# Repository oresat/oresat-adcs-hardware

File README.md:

# oresat-adcs-hardware

For more information on the OreSat project, please see <https://www.oresat.org/>!

## About this Repo

This repo contains the following projects:

* **The OreSat ADCS Card**
   * ADCS M0 microcontroller on its own OreSat Power Domain (OPD)
      * Power switch and LTC4300 that connects the M0 to:
         * BMI088 IMU (onboard the ADCS card)
         * LTC4305 2-Channel I2C Bus Multiplexer (one on each end cap via the backplane, end cards, and connectors to the end caps)
            * Two MMC5883MA magnetometers (two on each end cap, multiplexed by the LTC4305s)
      * Three STSPIN250s for the X, Y, and Z magnetorquers
   * Q1 Reaction Wheel OPD which powers the Q1 RW board
   * Q2 Reaction Wheel OPD which powers the Q2 RW board
   * Q3 Reaction Wheel OPD which powers the Q3 RW board
   * Q4 Reaction Wheel OPD which powers the Q4 RW board
* **OreSat RW boards**
   * Boards that run one of the four reaction wheels that we have.
   * Note that the "flat" version of the boards are for development

## LICENSE

Copyright the Portland State Aerospace Society, 2022.

This source describes Open Hardware that is licensed under CERN-OHL-S v2, or any later version.

You may redistribute and modify this source and make products using it under the terms of the CERN-OHL-S v2 (https://ohwr.org/cern_ohl_s_v2.txt).

This source is distributed WITHOUT ANY EXPRESS OR IMPLIED WARRANTY, INCLUDING OF MERCHANTABILITY, SATISFACTORY QUALITY AND FITNESS FOR A PARTICULAR PURPOSE. Please see the CERN-OHL-S v2 for applicable conditions.

Source location: https://github.com/oresat/

As per CERN-OHL-S v2 section 4, should You produce hardware based on this source, You must where practicable maintain the Source Location visible on the external case of the Gizmo or other products you make using this source.

# DEPRECATED - PLEASE EVENTUALLY REWRITE :)

## The OreSat Project
OreSat is an inter university collaboration to design an orbital vehicle. Once in orbit, the nanosatellite will engage in three missions. One of the missions is space testing a relatively new photovoltaic panel. The other missions require the ability to point at and maintain visual contact with a specified location. 
## Background Motivation   
In order to successfully complete these missions, OreSat will need to be able to articulate its orientation as well as its passive “drifting” spin (we’ll discuss what “passive spin” means a little later). 
Quick and reliable orientation adjustment and control will serve several purposes. It will allow the vehicle to direct its main camera, as well as giving it the ability to execute maneuvers that allow it to maintain visual and radio contact with a specific location. This makes taking photos and videos much easier, but it also allows us to have a segment of time to do large bandwidth data dumps to ground stations. This gives it the potential to do live video streaming. 
### Active Pointing
The method that was selected for active orientation on OreSat employs the use of internal spinning masses called reaction wheels. The basic principle is simple. If there is a free floating object and a section of it starts to spin, the rest of the body will react by spinning in the opposite direction. The spin rates are related, but not necessarily the same. If you’d like to look more into this, the concept is conservation of angular momentum. 
So the idea is that we have a pointing vector for Oresat (not poynting, that comes later), and an idea of the pointing vector to the location we would like to image. We simply take the difference, and then rotate the collective mass of all of the reaction wheels in the opposite direction until the satellite camera sees what we want it too.  
### Passive Spin Control
The term “passive spin” will be used to refer the net angular momentum of the nanosatellite. While the reaction wheels are active, they are able to control the direction and spin of the frame of the satellite, but only by effectively redistributing the momentum from the frame into the reaction wheel masses. The reaction wheels are incapable of altering the net angular momentum. The need for being able to modify the net momentum vector of the satellite helps alleviate the burden of two issues. The issues are thermal regulation and power generation. OreSat only has photovoltaic panels of its elongated faces. To maximize the amount of power, the desired passive spin of the satellite would put the long axis perpendicular to the sun. This maximizes the surface of exposure. There is another part to the total momentum though, and that is its magnitude. The rate of spin effects several things, but most notably it affects the temperature gradient experience by OreSat. If the satellite has no spin, then the side that the sun is hitting will heat continuously until OreSat passes behind the earth. This can cause several issues, most simply that having a hot spot would increase the likelihood of an electrical system to failing. Another issue is that the hot spot will cause different amounts of expansion in different areas of the frame, increasing the likelihood of failure. Another issue that hot spots cause is a drop in efficiency of the solar panels, making rotation partially an energy problem as well. 
Adding an intentional spin to OreSat will even out the thermal load applied to 

The attitude control system (ACS) inside oresat needs to orientate the position of the cubesat in space. This will be acheived in two ways; With brushless DC motors (BLDC) and with Magnetorquers. We are designing a PCB that controls both systems.

Find the project design contraints at,
[Project Design Constraints](https://github.com/oresat/oresat-acs-board/blob/master/Project%20Design%20Constraints.md)

ACS Level 2 Block Diagram Version 3.2

### System Hardware Overview
[Deatailed Hardware Reference Guide](https://github.com/oresat/oresat-acs-board/tree/master/Component%20File)

### EagleCAD Files:
[Link to the EagleCAD schematics and board layouts](https://github.com/oresat/oresat-acs-board/tree/master/eaglecad)

### Manufacturing Photos:
[Manufacturing photos of board layouts and CAD model of mounting strategy](https://github.com/oresat/oresat-acs-board/tree/master/Manufacturing%20photos)

### Capstone Poster:
[Link to Capstone poster in Google Drive](https://docs.google.com/presentation/d/1KBfbX376Y7nvsIXe14JdyOgP9TMmgJlgeOiYP8BOekc/edit#slide=id.p1)

### System Firmware:
[Check here for the firmware information](https://github.com/oresat/oresat-firmware/wiki/ACS-Firmware)

### Research and Tutorials / Ramp Up Documents:
Brushless DC (BLDC) motor control is a challenging form of motor control. We found numerous helpful tutorials and references.
[Link to research references and bibliography, start here for a ramp up on ACS](https://github.com/oresat/oresat-acs-board/blob/master/Ramp%20Up.md)

## Final Product:

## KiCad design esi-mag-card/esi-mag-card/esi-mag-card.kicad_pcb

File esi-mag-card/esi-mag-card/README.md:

---
title: "**OreSat Mag Card**"
subtitle: |
  **Fabrication and Assembly Information**\
  For build TIME-STAMP
fontsize: 10pt
geometry:
  - margin=0.5in
toc: true
toc-depth: 2
colorlinks: true
urlcolor: blue
---

\newpage

# About this Board

## Board Description

The OreSat Mag Card handles three things for the open source [OreSat CubeSat system](https://www.oresat.org/):

- Reads the four magnetometers located on the end caps of the satellite and broadcasts the data on the CAN bus.
- Reads the 6 DOF inertial measurement unit (IMU) and broadcasts the data on the CAN bus (mostly just the gyroscopes).
- Runs the three magnetorquers based on commands from the C3 via the CAN bus.

## Documentation Links

- Mag card hardware Git repository: <https://github.com/oresat/oresat-adcs-hardware>
- **TODO:** Mag card Design Notes + Design Review Notes

## Documentation Files

| Filename                        | Notes                                    |
| ------------------------------- | ---------------------------------------- |
| README.pdf                      | This README file                         |
| PROJECT-NAME-outline.dxf        | Board outline (with holes) in DXF format |
| PROJECT-NAME-pcba.step          | 3D model of PCBA (with components)       |
| PROJECT-NAME-render-bot.jpg     | Render of the top of the 3D model        |
| PROJECT-NAME-render-bot.jpg     | Render of the bottom of the 3D model     |
| PROJECT-NAME-schematic.pdf      | PDF of board schematics                  |

## Contact Information

- Website: <https://www.oresat.org/>
- Email: <oresat@pdx.edu>
- Instagram: @pdxaerospace

## Board Renders

{width=50%}
{width=50%}

\newpage

# Printed Circuit Board (PCB) Fabrication Information

## Board Info

- 4 layer board
- Bounding box is 99.8 x 94.6 mm (3.93 x 3.72 in)
- Board thickness is 1.59 mm (0.063 inch)

## Board Requirements

- Design Rules
    - Minimum Trace / Space design rules
       - Outer layers: 0.127 mm (5.0 mil) / 0.127 mm (5.0 mil)
       - Inner layers: 0.127 mm (5.0 mil) / 0.127 mm (5.0 mil)
    - Outer dimension router tolerance: +/- 0.254 mm (10.0 mil)
    - Hole placement tolerance: +/- 0.075 mm (3.0 mil)
    - Inner tab routed slot tolerance: +/- 0.254 mm (10.0 mil)
- Drills
   - Drill Positional Tolerance: 0.051 mm (2.0 mil)
   - Drill Size tolerance: +/- 0.064 mm (2.5 mil)
- Plated/Un-plated holes
  - There are 8 un-plated (NPT) holes
  - There are 730 plated through (PTH) holes
  - PTH minimum diameter: 0.254 mm (10 mil)
  - PTH minimum annulus: 0.102 mm (4 mil) radius
- Outline/Routing
  - Requires a 1.0 mm or smaller diameter routing bit
- Slots/Cutouts
  - There is one cutout.
- There are 3 fiducials on the top layer.
- Panel tabs ("mouse bites")
   - Card edges must be smooth; no mouse bites or other intrusions into the card outline.
   - If external mouse bites are required, minimize and customer will remove by hand before assembly.
- If not otherwise specified, build to IPC 6012 Class 2 or better.

## Materials

- No controlled impedance.
- Outer layers must be 1 oz Copper, inner layers can be 0.5 or 1.0 oz Copper.
- Isola FR408HR or material recommended.
- Board Surface treatment should be ENIG, althogh immersion Silver is acceptable.
- White silkscreen on top and bottom surface
- Taiyo PSR-4000 or equivalent soldermask on top and bottom, no requirements for color.

## Suggested Stack Up

| Layer         | Thickness           | Notes                                        |
|---------------|---------------------|----------------------------------------------|
| Top Copper    | 0.043 mm /  1.7 mil |  Layer 1 foil, 1 oz Cu after plating         |
| prepreg       | 0.200 mm /  7.9 mil |  Prepreg - Isola FR408HR 2113                |
| Layer 2       | 0.018 mm /  0.7 mil |  Layer 2 foil, 0.5 oz Cu                     |
| Core          | 0.991 mm /   39 mil |  Core Isola FR408HR                          |
| Layer 3       | 0.018 mm /  0.7 mil |  Layer 3 foil, 0.5 oz Cu                     |
| prepreg       | 0.200 mm /  7.9 mil |  Prepreg - Isola FR408HR 2113                |
| Bottom Copper | 0.043 mm /  1.7 mil |  Layer 4 foil, 1 oz copper after plating     |
| **Total Stackup** | **1.588 mm / 62.5 mil** |                                      |

## Array / Panel Information

- Coordinate with Contract Manufacturer (CM) for optimal size of this panel.
- If no feedback from CM, then produce single boards (no panel).

## Fabrication Files

### IPC-2581 File

| Filename                 | Notes                                   |
| ------------------------ | --------------------------------------- |
| PROJECT-NAME-ipc2581.xml | IPC-2581 board information file         |

### Legacy PCB Files

| Filename                      | Notes                                         |
| ------------------------------| --------------------------------------------- |
| PROJECT-NAME-Edge_Cuts.gbr    | RS274X file for the dimension (outline) layer |
| PROJECT-NAME-F_Silkscreen.gbr | RS274X file for the top silkscreen            |
| PROJECT-NAME-F_Mask.gbr       | RS274X file for the top soldermask            |
| PROJECT-NAME-F_Cu.gbr         | RS274X file for the top copper layer          |
| PROJECT-NAME-In1_Cu.gbr       | RS274X file for the layer 2 copper            |
| PROJECT-NAME-In2_Cu.gbr       | RS274X file for the layer 3 copper            |
| PROJECT-NAME-B_Cu.gbr         | RS274X file for the bottom copper layer       |
| PROJECT-NAME-B_Mask.gbr       | RS274X file for the bottom soldermask         |
| PROJECT-NAME-B_Silkscreen.gbr | RS274X file for the bottom silkscreen         |
| PROJECT-NAME-NPTH.drl         | Excellon file for non-plated through holes    |
| PROJECT-NAME-PTH.drl          | Excellon file for plated through holes        | 

\newpage

# Printed Circuit Board Assembly (PCBA) Information

## Assembly Info

- This PCBA is surface mount (SMT) components with 4 through-hole (TH) components.
- Components are only on the top side of the board.

## Assembly Requirements

- Assemble to IPC Class 2 or better
- Bake components that are not moisture sealed to appropriate levels as required.
- Solder paste MUST be leaded.
- Aqueous flux and wash strongly preferred.
   - Clean to NASA Standard "Visibly Clean (VC)": No particles or residues are visible to the naked eye.
- No conformal coating.
- Ship in antistatic protective bag

## Component Specific Assembly Information

- No specific requirements.

## Assembly Files

### IPC-2581 File

| Filename                 | Notes                           |
| ------------------------ | ------------------------------- |
| PROJECT-NAME-ipc2581.xml | IPC-2581 board information file |

### Bill of Materials (BOM)

| Filename             | Description                            |
| -------------------- | -------------------------------------- |
| PROJECT-NAME-bom.csv | BOM in Comma Separated Variable format |

### Solder Paste Stencils

| Filename                 | Notes                                            |
| ------------------------ | ------------------------------------------------ |
| PROJECT-NAME-B_Paste.gbr | RS274X file for top/front solder paste stencil   |
| PROJECT-NAME-F_Paste.gbr | RS274X file for bottom/back solder paste stencil |

### Mounting/Placement Location

| Filename            | Description                                 |
| ------------------- | ------------------------------------------- |
| PROJECT-NAME-3u.pos | Pick and place locations for components     |

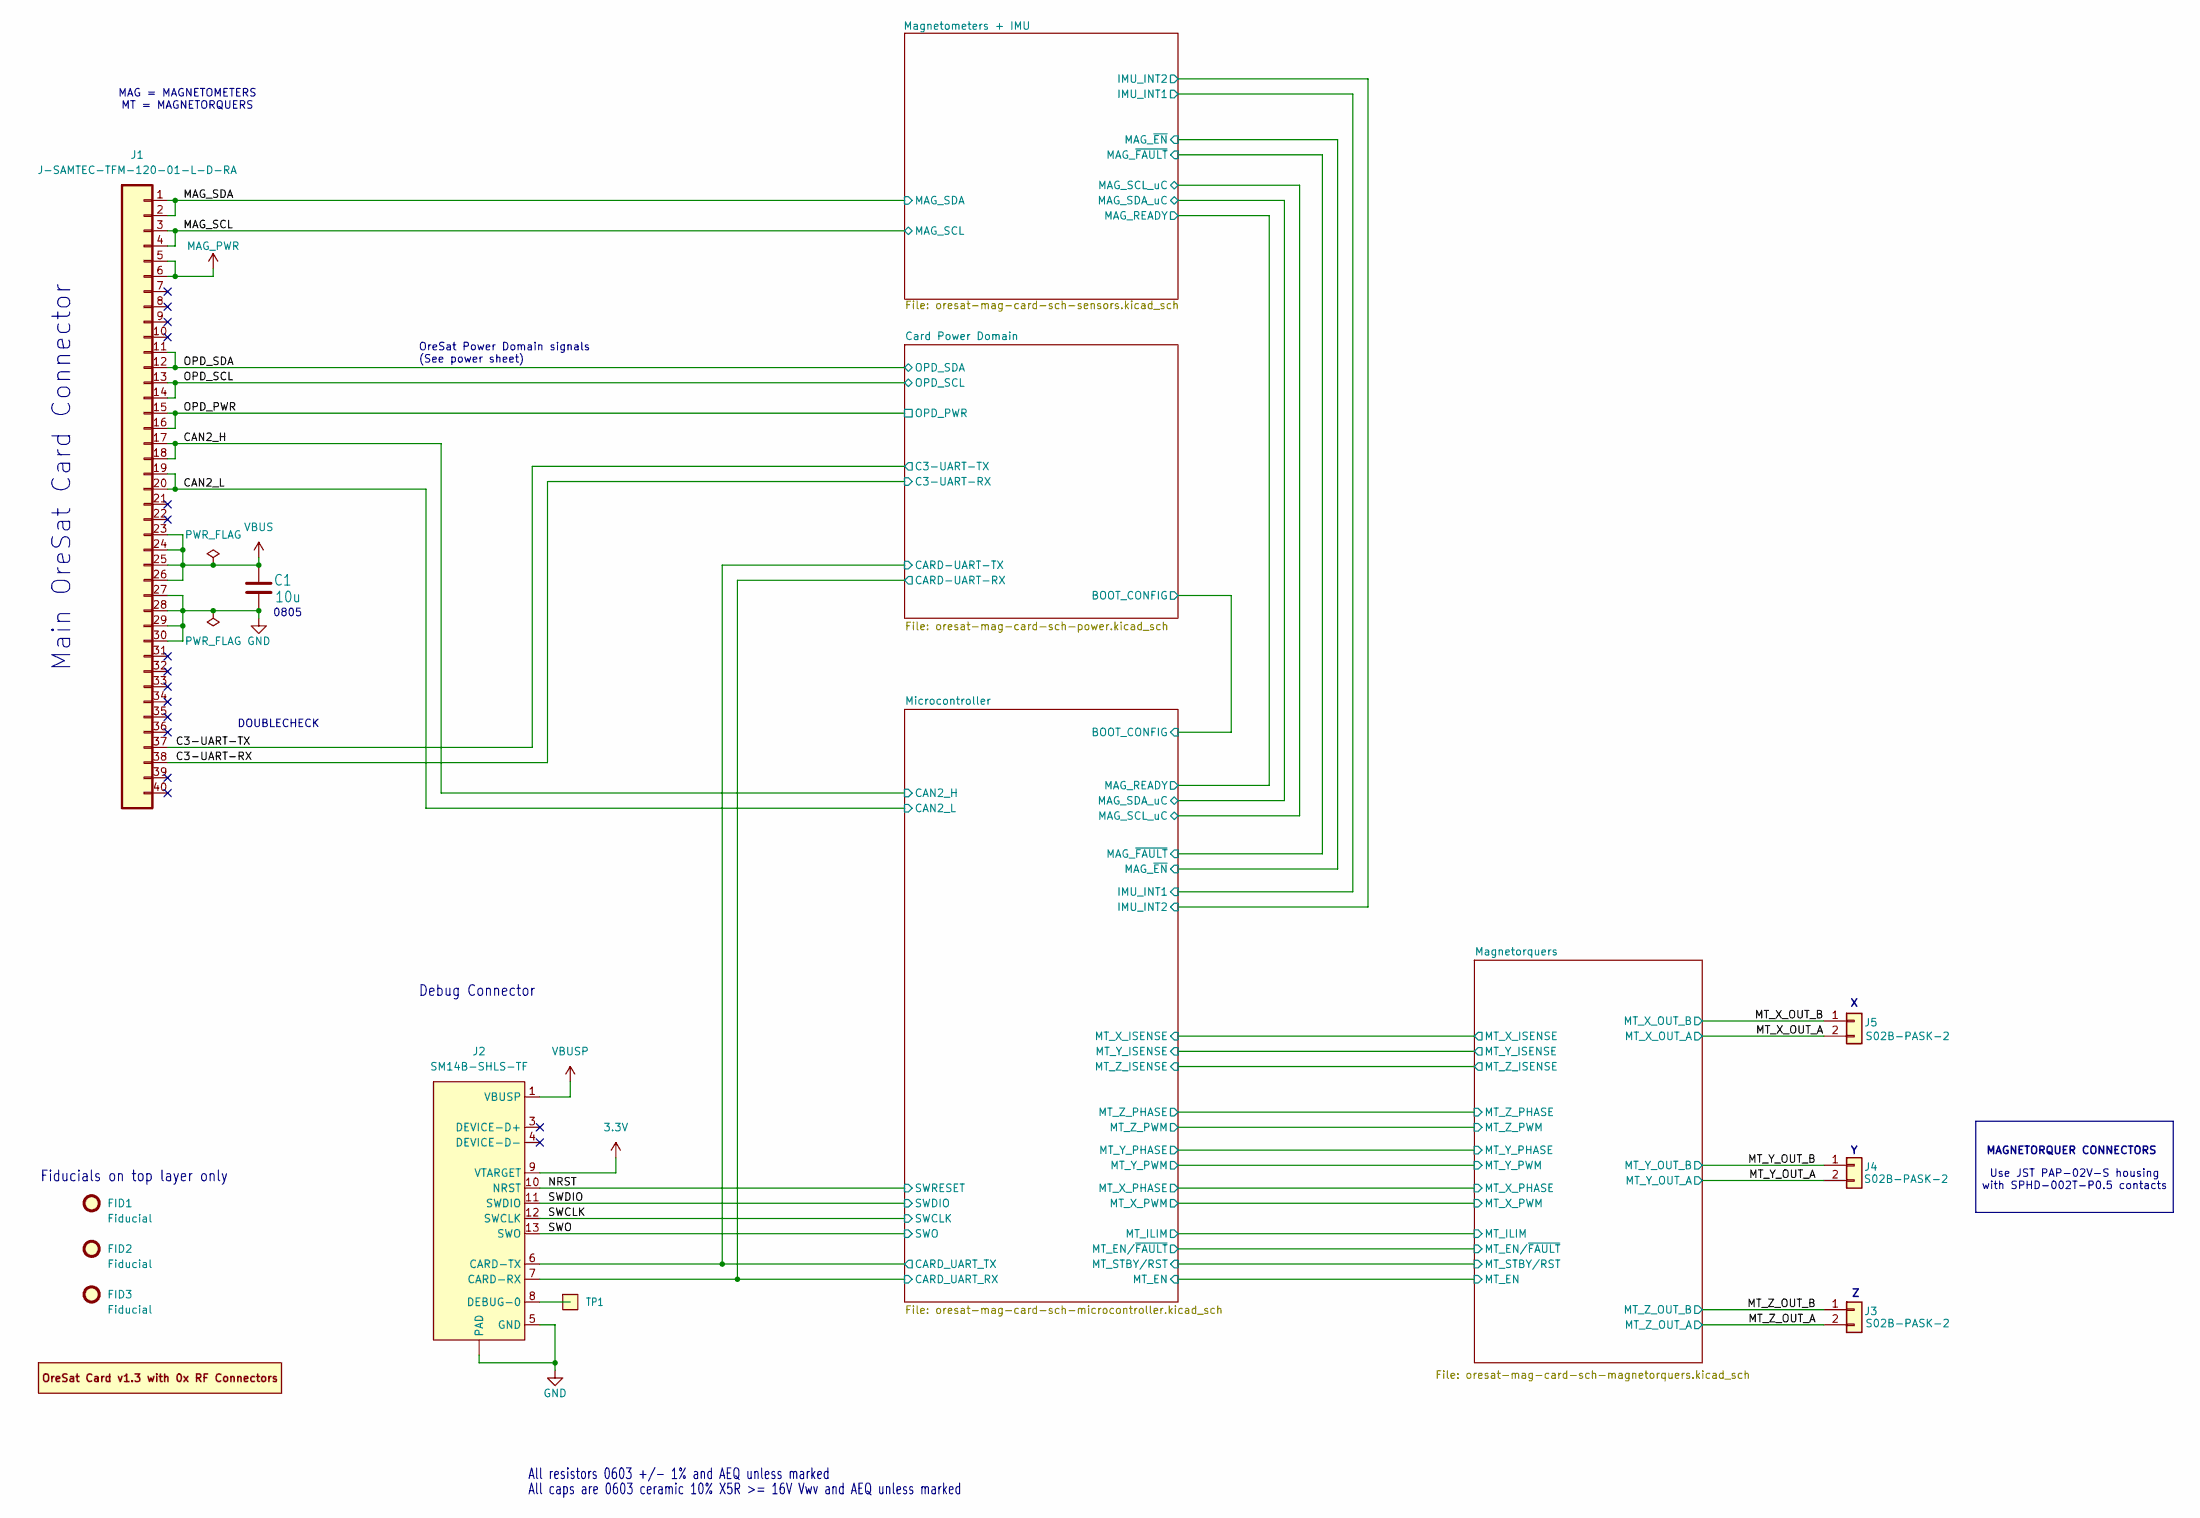
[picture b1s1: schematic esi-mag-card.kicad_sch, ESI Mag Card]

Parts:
C1: 10u; 0805-B-NOSILK; MPN GRT21BC71E106KE13K
FID1, FID2, FID3: Fiducial; Fiducial_1mm_Mask2mm
J1: J-SAMTEC-TFM-120-01-L-D-RA; J-SAMTEC-TFM-120-X1-XXX-D-RA; MPN TFM-120-01-L-D-RA
J2: SM14B-SHLS-TF; J-JST-SM14BSHLSTF; MPN SM14B-SHLS-TF
J3, J4, J5: S02B-PASK-2; JST-S02BPASK2LFSN; MPN S02B-PASK-2
PCB1: ORESAT-CARD-V1.3-GENERIC-0RF; ORESAT-CARD-V1.3-0RF; MPN N/A
TP1: Test-Point; TestPoint-0.75mm-th

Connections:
3.3V: J2.9 (VTARGET); also elsewhere on the board
/C3-UART-RX: J1.38; also elsewhere on the board
/C3-UART-TX: J1.37; also elsewhere on the board
/CAN2_H: J1.17, J1.18; also elsewhere on the board
/CAN2_L: J1.19, J1.20; also elsewhere on the board
/Card Power Domain/CARD-UART-RX: J2.7 (CARD-RX); also elsewhere on the board
/Card Power Domain/CARD-UART-TX: J2.6 (CARD-TX); also elsewhere on the board
/MAG_SCL: J1.3, J1.4; also elsewhere on the board
/MAG_SDA: J1.1, J1.2; also elsewhere on the board
/MT_X_OUT_A: J5.2; also elsewhere on the board
/MT_X_OUT_B: J5.1; also elsewhere on the board
/MT_Y_OUT_A: J4.2; also elsewhere on the board
/MT_Y_OUT_B: J4.1; also elsewhere on the board
/MT_Z_OUT_A: J3.2; also elsewhere on the board
/MT_Z_OUT_B: J3.1; also elsewhere on the board
/NRST: J2.10 (NRST); also elsewhere on the board
/OPD_PWR: J1.15, J1.16; also elsewhere on the board
/OPD_SCL: J1.13, J1.14; also elsewhere on the board
/OPD_SDA: J1.11, J1.12; also elsewhere on the board
/SWCLK: J2.12 (SWCLK); also elsewhere on the board
/SWDIO: J2.11 (SWDIO); also elsewhere on the board
/SWO: J2.13 (SWO); also elsewhere on the board
GND: C1.2, J1.27, J1.28, J1.29, J1.30, J2.5 (GND), J2.14 (GND), J2.15 (PAD), J2.16 (PAD); also elsewhere on the board
MAG_PWR: J1.5, J1.6; also elsewhere on the board
unnamed: J2.8 (DEBUG-0), TP1.1 (1_1)
VBUS: C1.1, J1.23, J1.24, J1.25, J1.26; also elsewhere on the board
VBUSP: J2.1 (VBUSP), J2.2 (VBUSP); also elsewhere on the board

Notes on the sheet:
All caps are 0603 ceramic 10% X5R >= 16V Vwv and AEQ unless marked
Main OreSat Card Connector
MAG = MAGNETOMETERS MT = MAGNETORQUERS
Use JST PAP-02V-S housing with SPHD-002T-P0.5 contacts
MAGNETORQUER CONNECTORS
DOUBLECHECK
Debug Connector
Fiducials on top layer only
0805
OreSat Power Domain signals (See power sheet)
All resistors 0603 +/- 1% and AEQ unless marked

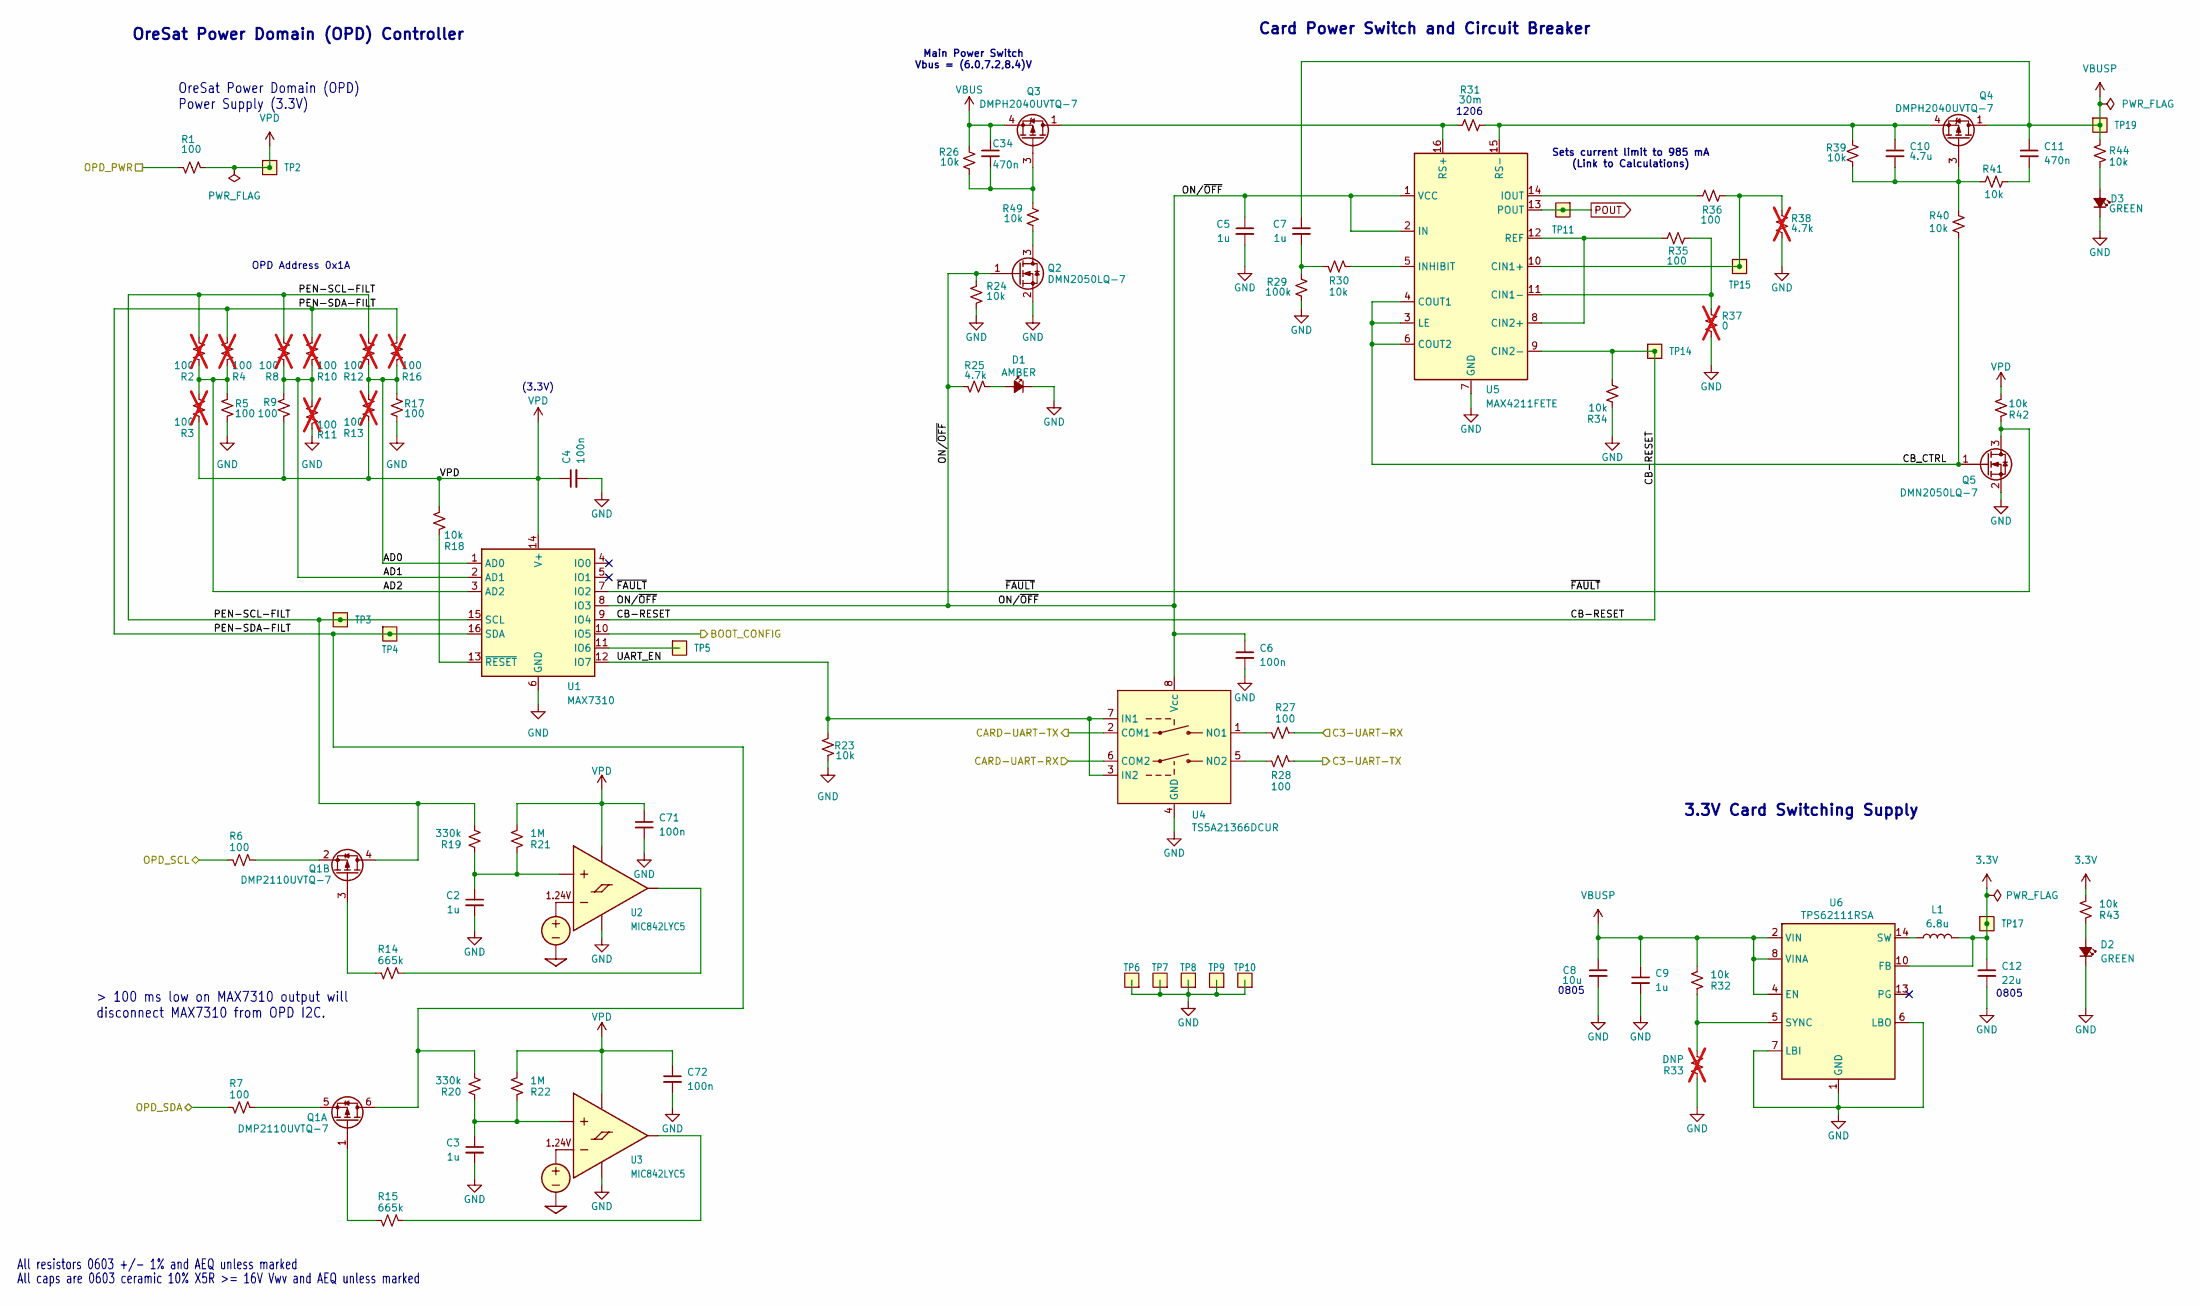
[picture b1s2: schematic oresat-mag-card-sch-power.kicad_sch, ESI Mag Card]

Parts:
C2, C3, C5, C7, C9: 1u; 0603-C-NOSILK; MPN GRT188R71E105KE13D
C4, C6, C71, C72: 100n; 0603-C-NOSILK; MPN C0603C104K5RACAUTO
C8: 10u; 0805-B-NOSILK; MPN GRT21BC71E106KE13K
C10: 4.7u; 0603-C-NOSILK; MPN GRT188C71C475KE13D
C11, C34: 470n; 0603-C-NOSILK; MPN C0603C474K3RACAUTO
C12: 22u; 0805-B-NOSILK; MPN GRT21BC81C226ME13L
D1: AMBER; LED_0603_1608Metric; MPN 150060AS75000
D2, D3: GREEN; LED_0603_1608Metric; MPN 150060GS75000
L1: 6.8u; L_ECS-MPI4040; MPN ECS-MPI4040R4-6R8-R
Q1: DMP2110UVTQ-7; SOT-23-6; MPN DMP2110UVTQ-7
Q2, Q5: DMN2050LQ-7; SOT-23; MPN DMN2050LQ-7
Q3, Q4: DMPH2040UVTQ-7; TSOT-23-6; MPN DMPH2040UVTQ-7
R1, R5, R6, R7, R9, R17, R27, R28, R35, R36: 100; 0603-C-NOSILK; MPN RMCF0603FT100R
R2, R3, R4, R8, R10, R11, R12, R13, R16: 100; 0603-C-NOSILK; MPN RMCF0603FT100R; not fitted
R14, R15: 665k; 0603-C-NOSILK; MPN RMCF0603FT665K
R18, R23, R24, R26, R30, R32, R34, R39, R40, R41, R42, R43, R44, R49: 10k; 0603-C-NOSILK; MPN RMCF0603FT10K0
R19, R20: 330k; 0603-C-NOSILK; MPN RMCF0603FT330K
R21, R22: 1M; 0603-C-NOSILK; MPN RMCF0603FT1M00
R25: 4.7k; 0603-C-NOSILK; MPN RMCF0603FT4K70
R29: 100k; 0603-C-NOSILK; MPN RMCF0603FT100K
R31: 30m; 1206-C; MPN CSR1206FK30L0
R33: DNP; 0603-C-NOSILK; not fitted
R37: 0; 0603-C-NOSILK; MPN RMCF0603ZT0R00; not fitted
R38: 4.7k; 0603-C-NOSILK; MPN RMCF0603FT4K70; not fitted
TP2, TP3, TP4, TP5, TP6, TP7, TP8, TP9, TP10, TP11, TP14, TP15, TP17, TP19: Test-Point; TestPoint-0.75mm-th
U1: MAX7310; QFN-16-1EP_4x4mm_P0.65mm_EP2.1x2.1mm; MPN MAX7310ATE+
U2, U3: MIC842LYC5; SOT-353_SC-70-5; MPN MIC842LYC5-TR
U4: TS5A21366DCUR; VSSOP-8_2.3x2mm_P0.5mm; MPN TS5A21366DCUR
U5: MAX4211FETE; QFN-16-1EP_4x4mm_P0.65mm_EP2.1x2.1mm; MPN MAX4211FETE
U6: TPS62111RSA; Texas_RSA_VQFN-16-1EP_4x4mm_P0.65mm_EP2.7x2.7mm; MPN TPS62111RSA

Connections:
3.3V: C12.1, L1.2, R43.2, TP17.1 (1_1), U6.10 (FB); also elsewhere on the board
/C3-UART-RX: R27.1; also elsewhere on the board
/C3-UART-TX: R28.1; also elsewhere on the board
/Card Power Domain/AD0: R12.1, R13.2, R16.1, R17.2, U1.1 (AD0)
/Card Power Domain/AD1: R8.1, R9.2, R10.1, R11.2, U1.2 (AD1)
/Card Power Domain/AD2: R2.1, R3.2, R4.1, R5.2, U1.3 (AD2)
/Card Power Domain/BOOT_CONFIG: U1.10 (IO5); also elsewhere on the board
/Card Power Domain/CARD-UART-RX: U4.6 (COM2); also elsewhere on the board
/Card Power Domain/CARD-UART-TX: U4.2 (COM1); also elsewhere on the board
/Card Power Domain/CB-RESET: R34.2, TP14.1 (1_1), U1.9 (IO4), U5.9 (CIN2-)
/Card Power Domain/CB_CTRL: Q5.1 (G), R40.1, U5.3 (LE), U5.4 (COUT1), U5.6 (COUT2)
/Card Power Domain/ON/~OFF: C5.1, C6.1, Q2.1 (G), R24.1, R25.2, U1.8 (IO3), U4.8 (Vcc), U5.1 (VCC), U5.2 (IN)
/Card Power Domain/PEN-SCL-FILT: Q1.4 (D), R2.2, R8.2, R12.2, R19.2, TP3.1 (1_1), U1.15 (SCL)
/Card Power Domain/PEN-SDA-FILT: Q1.6 (D), R4.2, R10.2, R16.2, R20.2, TP4.1 (1_1), U1.16 (SDA)
/Card Power Domain/UART_EN: R23.2, U1.12 (IO7), U4.3 (IN2), U4.7 (IN1)
/Card Power Domain/~FAULT: Q5.3 (D), R42.1, U1.7 (IO2)
/OPD_PWR: R1.2; also elsewhere on the board
/OPD_SCL: R6.2; also elsewhere on the board
/OPD_SDA: R7.2; also elsewhere on the board
GND: C2.2, C3.2, C4.2, C5.2, C6.2, C8.2, C9.2, C12.2, C71.2, C72.2, D1.1 (K), D2.1 (K), D3.1 (K), Q2.2 (S), Q5.2 (S), R5.1, R11.1, R17.1, R23.1, R24.2, R29.2, R33.1, R34.1, R37.2, R38.2, TP6.1 (1_1), TP7.1 (1_1), TP8.1 (1_1), TP9.1 (1_1), TP10.1 (1_1), U1.6 (GND), U1.17 (GND), U2.2 (GND), U3.2 (GND), U4.4 (GND), U5.7 (GND), U5.17 (GND), U6.1 (GND), U6.6 (LBO), U6.7 (LBI), U6.9 (GND), U6.11 (GND), U6.12 (GND), U6.16 (GND), U6.17 (GND); also elsewhere on the board
unnamed: C7.2, R29.1, R30.2
unnamed: C11.2, R41.1
unnamed: D1.2 (A), R25.1
unnamed: D2.2 (A), R43.1
unnamed: D3.2 (A), R44.1
unnamed: L1.1, U6.14 (SW), U6.15 (SW)
unnamed: Q1.1 (G), R15.2
unnamed: Q1.5 (S), R7.1
unnamed: Q1.3 (G), R14.2
unnamed: Q1.2 (S), R6.1
unnamed: Q2.3 (D), R49.2
unnamed: C34.2, Q3.3 (G), R26.2, R49.1
unnamed: C10.2, Q4.3 (G), R39.1, R40.2, R41.2
unnamed: C10.1, Q4.4 (S), R31.2, R39.2, U5.15 (RS-)
unnamed: TP5.1 (1_1), U1.11 (IO6)
unnamed: R18.1, U1.13 (~RESET)
unnamed: C2.1, R19.1, R21.1, U2.1 (INP)
unnamed: R14.1, U2.4 (OUT)
unnamed: C3.1, R20.1, R22.1, U3.1 (INP)
unnamed: R15.1, U3.4 (OUT)
unnamed: R27.2, U4.1 (NO1)
unnamed: R28.2, U4.5 (NO2)
unnamed: R36.1, R38.1, TP15.1 (1_1), U5.10 (CIN1+)
unnamed: R35.1, R37.1, U5.11 (CIN1-)
unnamed: R35.2, U5.8 (CIN2+), U5.12 (REF)
unnamed: R30.1, U5.5 (INHIBIT)
unnamed: R36.2, U5.14 (IOUT)
unnamed: Q3.1 (D), Q3.2 (D), Q3.5 (D), Q3.6 (D), R31.1, U5.16 (RS+)
unnamed: R32.1, R33.2, U6.5 (SYNC)
POUT: TP11.1 (1_1), U5.13 (POUT)
VBUS: C34.1, Q3.4 (S), R26.1; also elsewhere on the board
VBUSP: C7.1, C8.1, C9.1, C11.1, Q4.1 (D), Q4.2 (D), Q4.5 (D), Q4.6 (D), R32.2, R44.2, TP19.1 (1_1), U6.2 (VIN), U6.3 (VIN), U6.4 (EN), U6.8 (VINA); also elsewhere on the board
VPD: C4.1, C71.1, C72.1, R1.1, R3.1, R9.1, R13.1, R18.2, R21.2, R22.2, R42.2, TP2.1 (1_1), U1.14 (V+), U2.5 (VDD), U3.5 (VDD)

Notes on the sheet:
Sets current limit to 985 mA (Link to Calculations)
OPD Address 0x1A
3.3V Card Switching Supply
OreSat Power Domain (OPD) Power Supply (3.3V)
> 100 ms low on MAX7310 output will disconnect MAX7310 from OPD I2C.
Card Power Switch and Circuit Breaker
1206
(3.3V)
All resistors 0603 +/- 1% and AEQ unless marked
All caps are 0603 ceramic 10% X5R >= 16V Vwv and AEQ unless marked
OreSat Power Domain (OPD) Controller
0805
Main Power Switch Vbus = (6.0,7.2,8.4)V

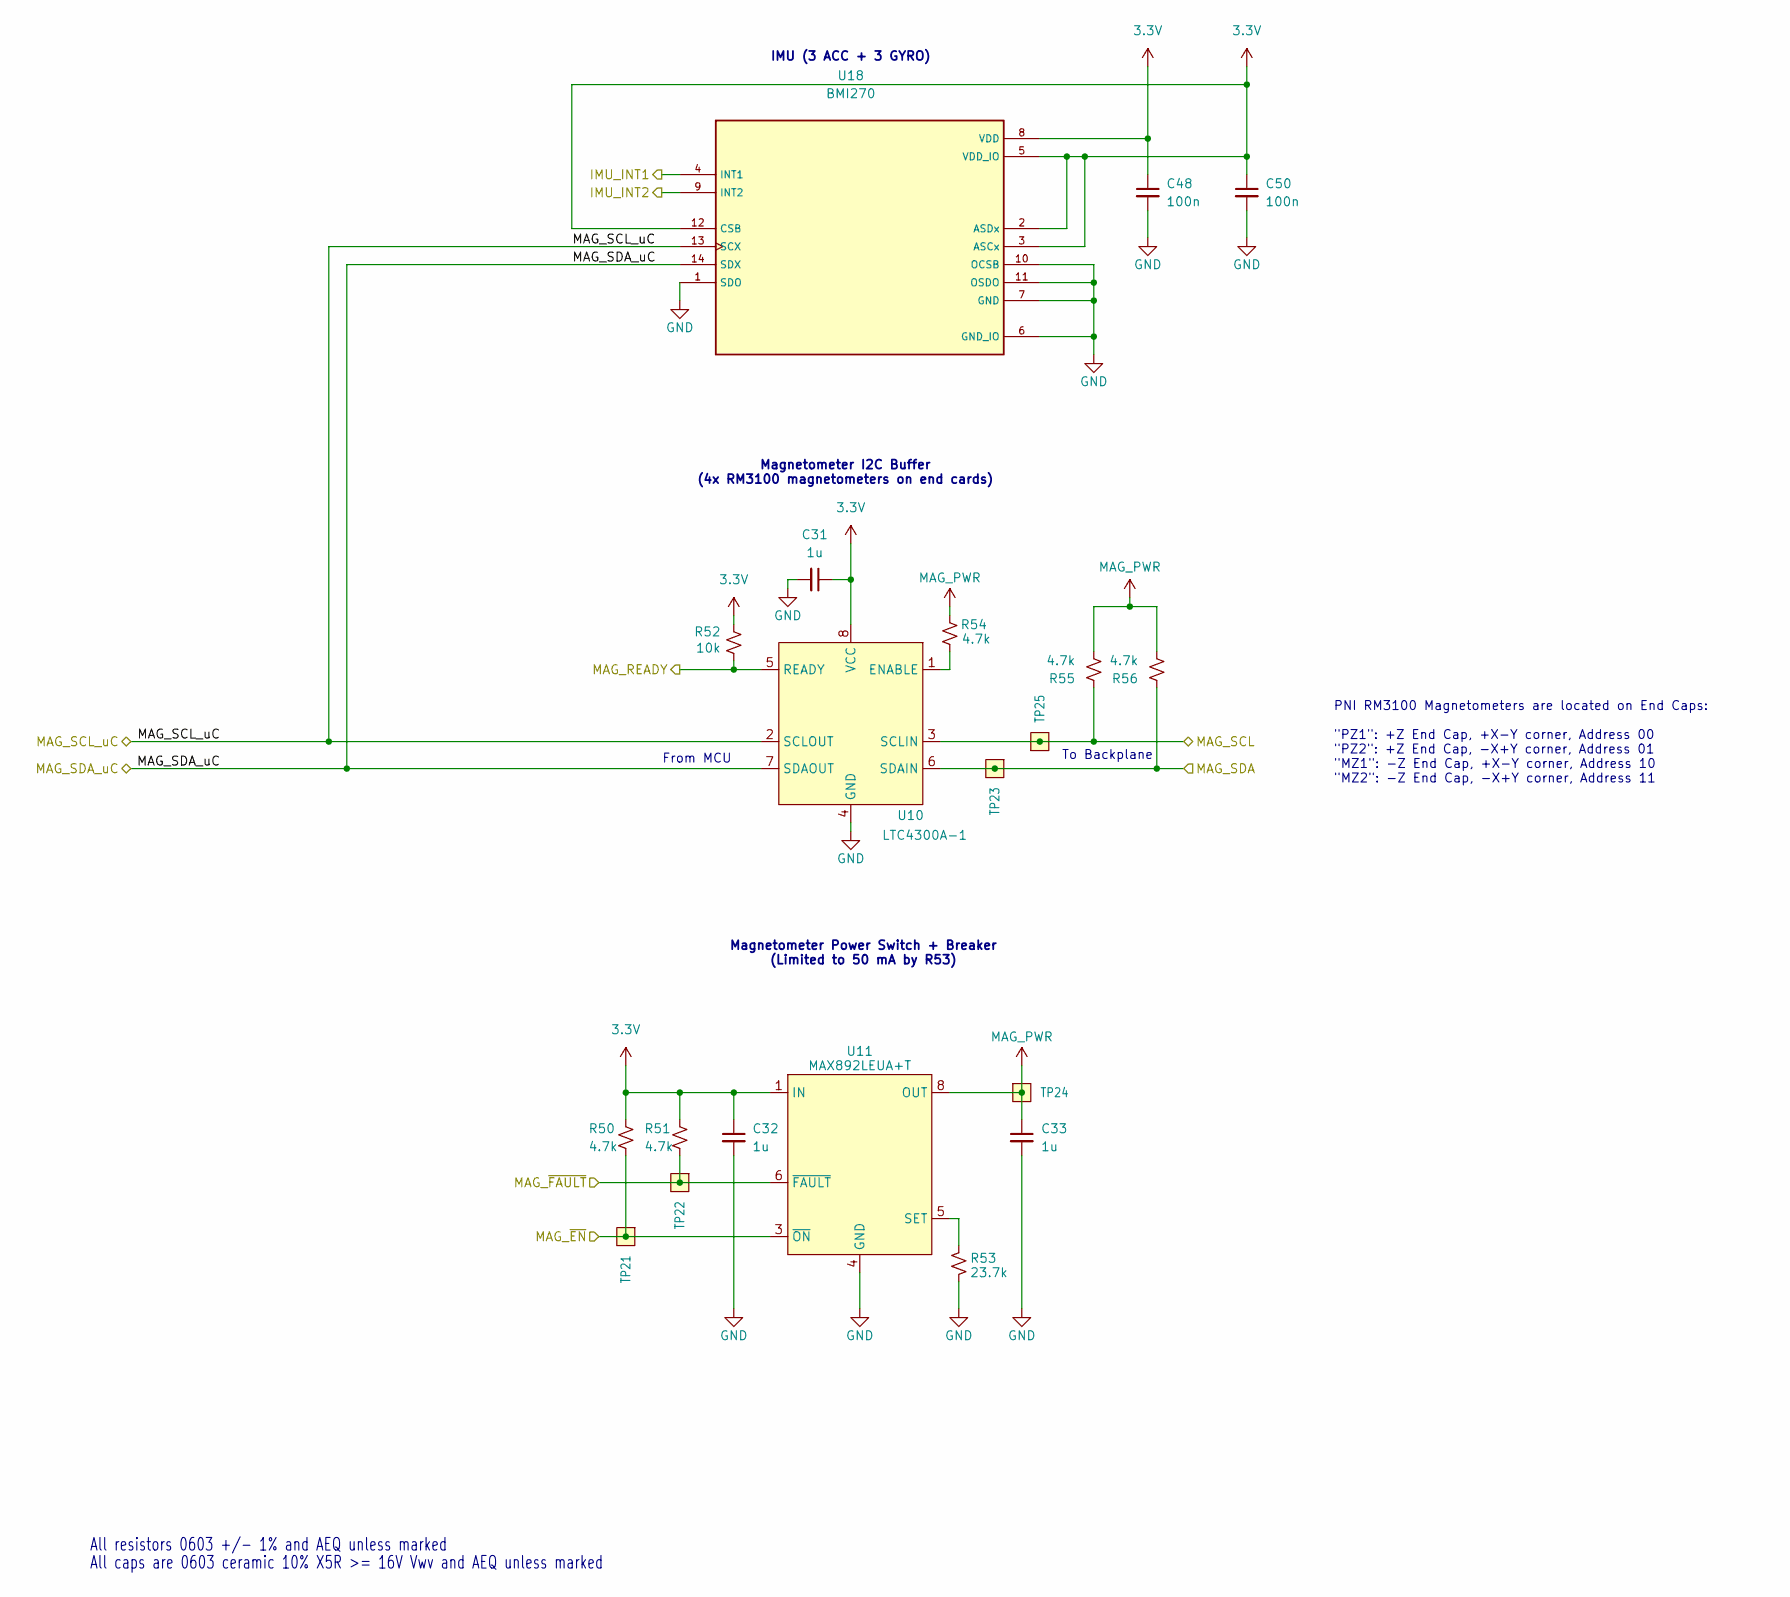
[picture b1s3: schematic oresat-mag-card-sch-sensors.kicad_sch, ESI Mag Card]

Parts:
C31, C32, C33: 1u; 0603-C-NOSILK; MPN GRT188R71E105KE13D
C48, C50: 100n; 0603-C-NOSILK; MPN C0603C103J5RACAUTO
R50, R51, R54, R55, R56: 4.7k; 0603-C-NOSILK; MPN RMCF0603FT4K70
R52: 10k; 0603-C-NOSILK; MPN RMCF0603FT10K0
R53: 23.7k; 0603-C-NOSILK; MPN RMCF0603FT23K7
TP21, TP22, TP23, TP24, TP25: Test-Point; TestPoint-0.75mm-th
U10: LTC4300A-1; MSOP-8_3x3mm_P0.65mm; MPN LTC4300A-1IMS8#TRPBF
U11: MAX892LEUA+T; MSOP-8_3x3mm_P0.65mm; MPN MAX892LEUA+T
U18: BMI270; PQFN50P300X250X97-14N; MPN BMI270

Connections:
3.3V: C31.1, C32.1, C48.1, C50.1, R50.2, R51.2, R52.2, U10.8 (VCC), U11.1 (IN), U11.2 (IN_2), U18.2 (ASDx), U18.3 (ASCx), U18.5 (VDD_IO), U18.8 (VDD), U18.12 (CSB); also elsewhere on the board
/MAG_SCL: R55.1, TP25.1 (1_1), U10.3 (SCLIN); also elsewhere on the board
/MAG_SDA: R56.1, TP23.1 (1_1), U10.6 (SDAIN); also elsewhere on the board
/Magnetometers + IMU/IMU_INT1: U18.4 (INT1); also elsewhere on the board
/Magnetometers + IMU/IMU_INT2: U18.9 (INT2); also elsewhere on the board
/Magnetometers + IMU/MAG_READY: R52.1, U10.5 (READY); also elsewhere on the board
/Magnetometers + IMU/MAG_SCL_uC: U10.2 (SCLOUT), U18.13 (SCX); also elsewhere on the board
/Magnetometers + IMU/MAG_SDA_uC: U10.7 (SDAOUT), U18.14 (SDX); also elsewhere on the board
/Magnetometers + IMU/MAG_~EN: R50.1, TP21.1 (1_1), U11.3 (~ON); also elsewhere on the board
/Magnetometers + IMU/MAG_~FAULT: R51.1, TP22.1 (1_1), U11.6 (~FAULT); also elsewhere on the board
GND: C31.2, C32.2, C33.2, C48.2, C50.2, R53.1, U10.4 (GND), U11.4 (GND), U18.1 (SDO), U18.6 (GND_IO), U18.7 (GND), U18.10 (OCSB), U18.11 (OSDO); also elsewhere on the board
MAG_PWR: C33.1, R54.2, R55.2, R56.2, TP24.1 (1_1), U11.7 (OUT_2), U11.8 (OUT); also elsewhere on the board
unnamed: R54.1, U10.1 (ENABLE)
unnamed: R53.2, U11.5 (SET)

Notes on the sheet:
PNI RM3100 Magnetometers are located on End Caps: "PZ1": +Z End Cap, +X-Y corner, Address 00 "PZ2": +Z End Cap, -X+Y corner, Address 01 "MZ1": -Z End Cap, +X-Y corner, Address 10 "MZ2": -Z End Cap, -X+Y corner, Address 11
To Backplane
All resistors 0603 +/- 1% and AEQ unless marked
IMU (3 ACC + 3 GYRO)
From MCU
All caps are 0603 ceramic 10% X5R >= 16V Vwv and AEQ unless marked
Magnetometer Power Switch + Breaker (Limited to 50 mA by R53)
Magnetometer I2C Buffer (4x RM3100 magnetometers on end cards)
